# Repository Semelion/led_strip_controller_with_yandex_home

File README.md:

# led_strip_controller_with_yandex_home
Контролер с возможностью подключения к умному дому Яндекс

Идея проекта сделать основу для проектов умного дома с интеграцией в умный дом Яндекс. Изначально возникла потребность управлять светодиодной лентой с возможностью димирования, но представленные контроллеры не внушали доверия

### Компоненты
- esp8266 для управления
- оптопары для управления транзисторами и другой нагрузкой 5 вольт
- транзистор IRF44N для управления светодиодной ленты
- кнопка без фиксации с подсветкой
- блок питания 12 вольт (расчитанный по мощности под ленту)
- понижающий dc-dc преобразователь для питания платы и компонентов

## Печатная плата
Печатная плата спроектирована в KiCad, исходники можно посмотреть в `kitchen_light_pcb/`, а библиотеки компенонтов использованные лежат в `kicad_lib`

Схема печатной платы

- Разъем J2 для подключения светодиодной ленты
- J1, J7 разьемы 12 вольт на вход
- J4, J8 разьемы 5 вольт на вход
- J6 разьем подключенный к ESP, для подключения чего либо если понадобится
- есть датчик температуры и влажности DHT22
- J5 задумывается для использования реле и кнопки, чтобы встроить в выключатель без нуля
- SW1 контакты для кнопки, в моем случае это внешняя кнопка, крепится в низ шкафа над плитой
- J3 контакты для подсветки кнопки

Разведение печатной платы

Печатная плата в 3D

Печатная плата в жизни, сделанная по методу ЛУТ

## Код
Файл с кодом: `controller_code/controller_code.ino`  
В коде необходимо прописать параметры под ваши условия:
``` cpp
#define ssid  "" //write your SSID
#define password  "" //write password
#define mqtt_server "" //url or ip mqtt server
#define mqtt_port 1883 //port for mqtt server
```
Тут необходимо указать данные вашего WIFI и MQTT сервера  
Как вариант найти MQTT сервер можно [тут.](https://mntolia.com/10-free-public-private-mqtt-brokers-for-testing-prototyping/)

Также надо прописать топики для управления лентой, они должны быть уникальными, особенно при использовании публичного сервера, так как кто нибудь может туда публиковать значения
```cpp
#define LAMP_STATE_TOPIC "kitchen/lamp/state" //поменять на свои
#define LAMP_POWER_TOPIC "kitchen/lamp/power"
```

Прошивать надо через Arduino IDE, гайд [тут.](https://wiki.iarduino.ru/page/wemos_start/)

### Подключение к Алисе
Интеграция в умный дом происходит через навык "Домовёнок Кузя", у автора есть подробные гайды на [сайте](https://alexstar.ru/smarthome) и на [Ютуб](https://www.youtube.com/watch?v=lm6nl2dc3VI&t=30s)

Необходимо будет зайти под своим аккаунтом Яндекс, настроить правила MQTT на включение, выключение и изменения яркости, а также создать виртуальное устройство к которому привязать правила MQTT

## Результат работы
<video controls>
  <source src="pics/video.mov" type="video/mp4">
</video>

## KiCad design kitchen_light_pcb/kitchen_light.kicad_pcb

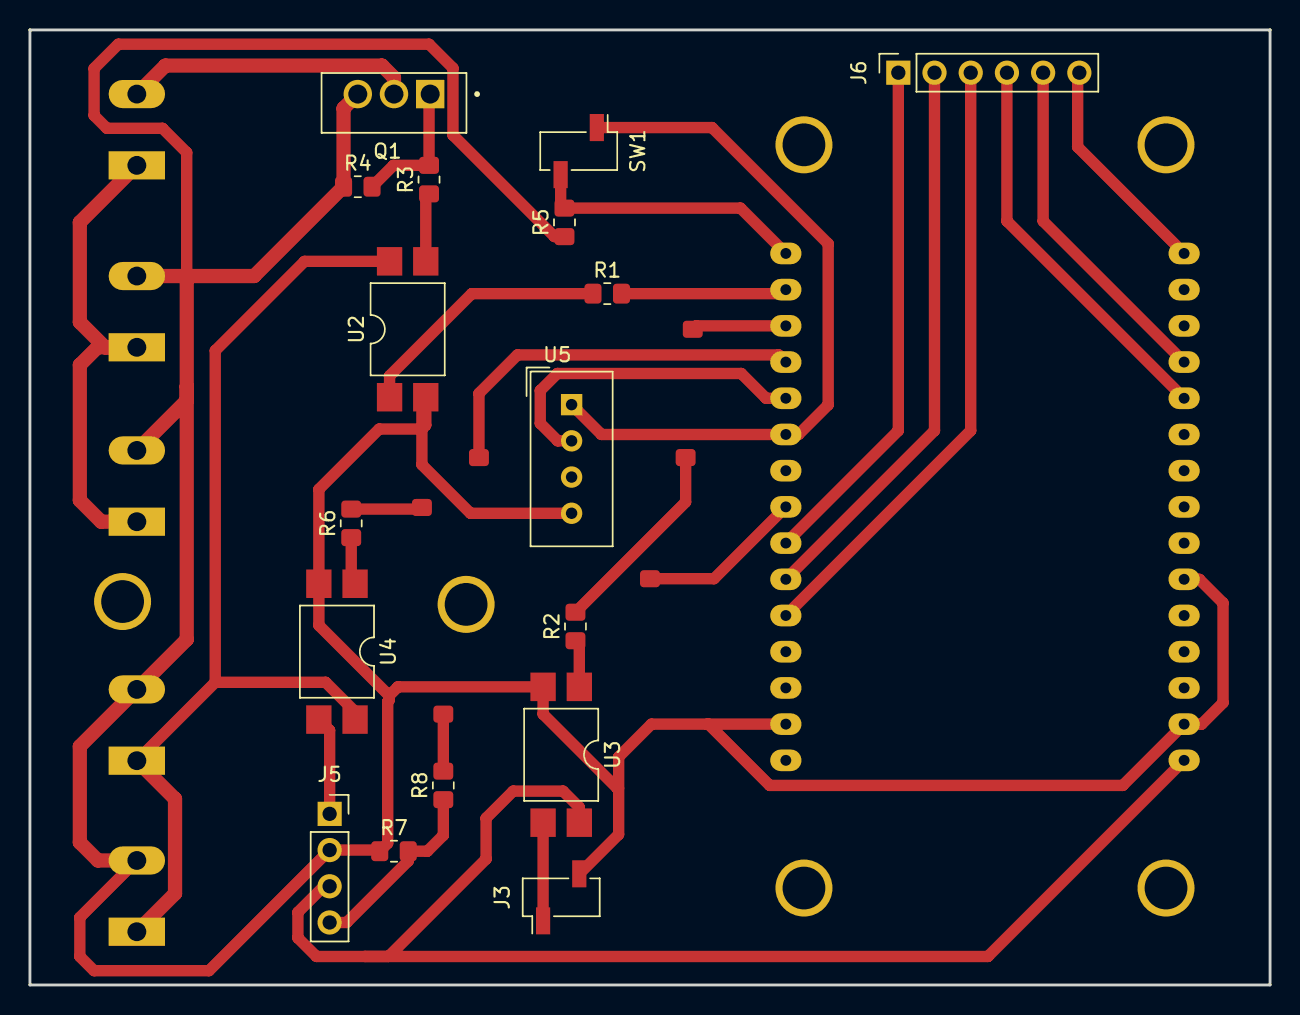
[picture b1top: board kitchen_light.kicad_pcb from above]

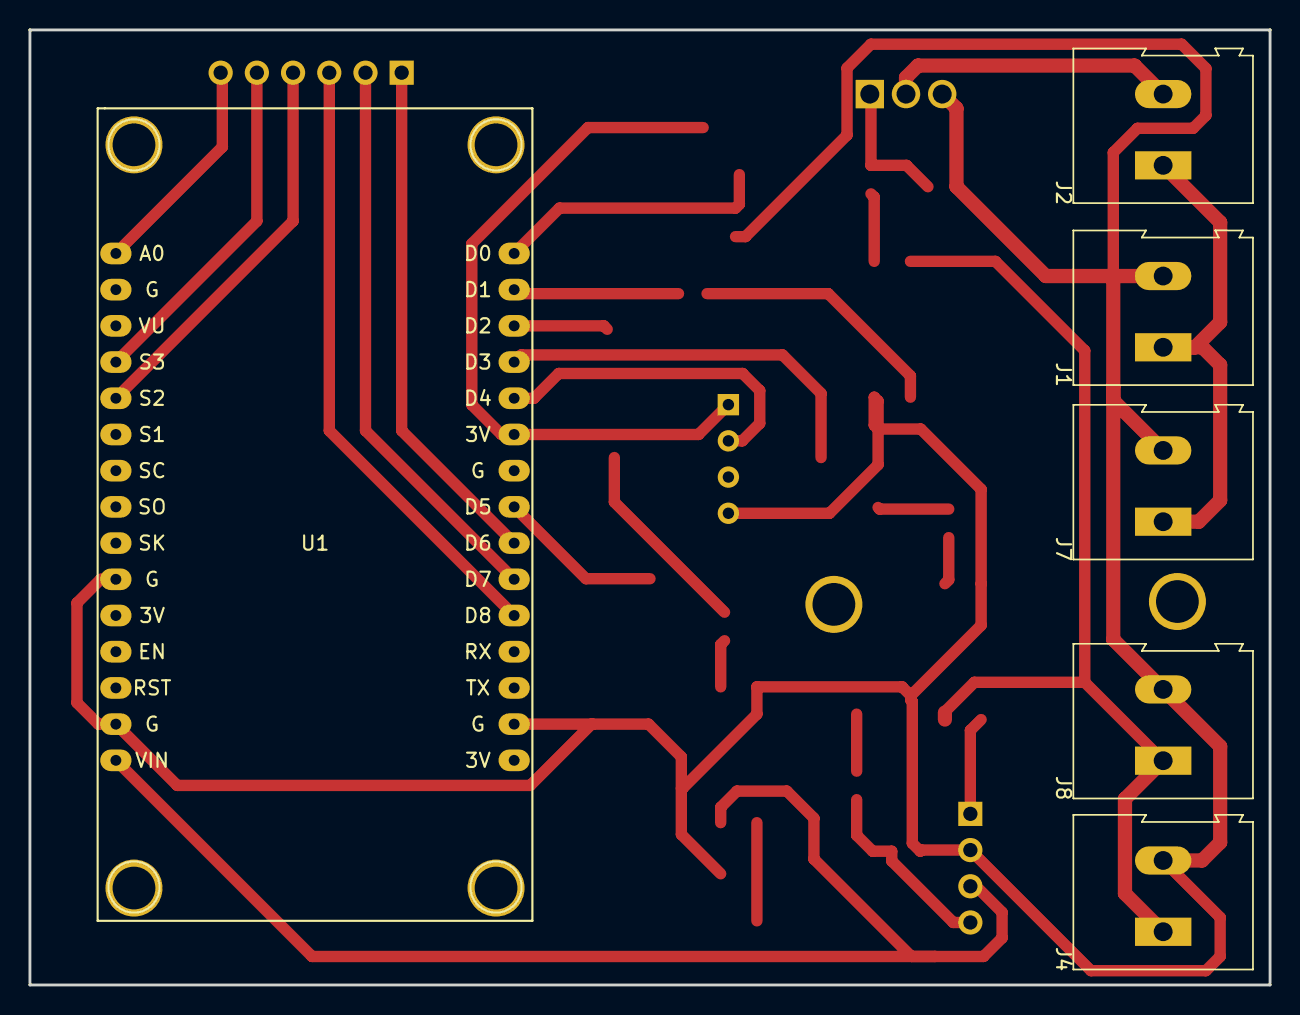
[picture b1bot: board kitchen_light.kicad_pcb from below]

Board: 2 copper layers, 87.0 x 67.0 mm, 23 parts (6 on the bottom side), 25 nets.

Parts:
J1, J7: 12v; TerminalBlock_Altech_AK300-2_P5.00mm
J2: led_strip; TerminalBlock_Altech_AK300-2_P5.00mm
J3: button_led; PinSocket_1x02_P2.54mm_Vertical_SMD_Pin1Left
J4, J8: 5v; TerminalBlock_Altech_AK300-2_P5.00mm
J5: relay+button; PinSocket_1x04_P2.54mm_Vertical
J6: Conn_01x06_Socket; PinSocket_1x06_P2.54mm_Vertical
Q1: IRFZ44N; TO254P1016X419X2286-3
R1, R2, R6, R8: 330R; R_0805_2012Metric_Pad1.20x1.40mm_HandSolder
R3: 100R; R_0805_2012Metric_Pad1.20x1.40mm_HandSolder
R4, R5, R7: 10K; R_0805_2012Metric_Pad1.20x1.40mm_HandSolder
SW1: button; PinSocket_1x02_P2.54mm_Vertical_SMD_Pin1Left
U1: NodeMCU1.0(ESP-12E); NodeMCU-LoLinV3
U2, U3, U4: LTV-817S; SMDIP-4_W9.53mm
U5: DHT11; Aosong_DHT11_5.5x12.0_P2.54mm

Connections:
+3.3V: SW1.1 (A), U1.11 (3.3V), U1.16 (3.3V), U1.25 (3.3V), U5.1 (VDD)
+5V: J4.1, J5.3, J8.1, U1.15 (VIN), U2.4, U3.4, U4.4
+12V: J1.1, J2.1, J7.1
GND: J1.2, J3.2, J4.2, J5.2, J7.2, J8.2, Q1.3, R4.1, R5.1, R7.1, U1.10 (GND), U1.14 (GND), U1.17 (GND), U1.24 (GND), U2.2, U3.2, U4.2, U5.4 (GND)
unnamed: J2.2, Q1.2
unnamed: J3.1, U3.3
unnamed: J5.1, U4.3
unnamed: J5.4, R7.2, R8.1
unnamed: J6.1, U1.22 (D6(GPIO12))
unnamed: J6.2, U1.21 (D7(GPIO13))
unnamed: J6.3, U1.20 (D8(GPIO15))
unnamed: J6.4, U1.5 (SD2(GPIO9))
unnamed: J6.5, U1.4 (SD3(GPIO10))
unnamed: J6.6, U1.1 (A0(ADC0))
unnamed: Q1.1, R3.2, R4.2
unnamed: R1.1, U2.1
unnamed: R2.1, U3.1
unnamed: R3.1, U2.3
unnamed: R6.1, U4.1
unnamed: R5.2, SW1.2 (A), U1.30 (D0(GPIO16))
unnamed: R1.2, U1.29 (D1(GPIO5))
unnamed: R2.2, U1.28 (D2(GPIO4))
unnamed: R6.2, U1.27 (D3(GPIO0))
unnamed: U1.26 (D4(GPIO2)), U5.2 (DATA)
unnamed: R8.2, U1.23 (D5(GPIO14))

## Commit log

2024-01-11 modified: README.md new file: controller_code/controller_code.ino new file: kicad_lib/IRFZ44N/IRFZ44N.kicad_sym new file: kicad_lib/IRFZ44N/IRFZ44N.pretty/TO254P1016X419X2286-3.kicad_mod new file: ki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
